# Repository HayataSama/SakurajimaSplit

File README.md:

# SakurajimaSplit

SakurajimaSplit is a 6x3 column stagger split mechanical keyboard. It's inspired by [Corne](https://github.com/foostan/crkbd), [Kyria](https://github.com/splitkb/kyria) and [Elephant42](https://github.com/illness072/elephant42).

> [!NOTE]
> The master branch contains the most recent commits and is not meant for production. Gerbers and production files are available as a github release.
>
> This project was was made in KiCad 9.0 and FreeCAD 1.0. In addition to KiCad's default libraries, I used the [ebastler's marbastlib](https://github.com/ebastler/marbastlib) footprint and symbol library and [zykrah's kicad-kle-placer](https://github.com/zykrah/kicad-kle-placer) plugin. Using other versions may introduce bugs and/or inconsistencies therefore is discouraged.

## Features

- QMK compatible
- Cherry MX switch profile
- 3-Key thumb cluster
- 10-Degree sideways tilt
- SSD1305 OLED display
- W25Q Flash Storage for storing animations
- USB-C connector

## Motivation

I've been interested in mechanical keyboard for a few years now. I got my endgame keyboard (Mode Envoy) a while back and it's been my daily driver since. A while ago I suddenly became interested in split mechanical keyboards. Something about them being tiny and portable, also having this cyberpunky feeling made them appealing to me.

Apparently ortholinear keyboards are also more comfortable to type on. (Not sure how true this is but now that I've built this keyboard and am using it on daily basis, I should say it feels so damn nice to type with!)

I'm also an electrical engineering student and I have some experience designing PCBs. With all these in mind I thought, why not? Why not build a fully custom keyboard, tailored exactly to my needs? A few months later and here we are!

## Why Sakurajima?

Because Mai Sakurajima is the best girl.

## The Journey and Some Notes

This was my first experience designing a keyboard (and a handheld device in general). My approach for designing the layout was to put my fingers on a piece of paper (in the supposedly most comfortable position) and mark under each of my fingertips to find the best position for the home row. Then I measured the distance between keys and rounded them up to the closest standard value. (keyboard "u" units).

For the thumb cluster in addition to the fingertip, I also marked my thumb's joint (MCP joint?) on the paper to find the center of the circle where the thumb keys would be placed. Then I did some basic geometry to find the angle and distance of each key with respect to the center.

I don't know if this is the best approach or even a good approach, but it was fairly easy to do and the end result is great.

Let's talk about electronics. I know I've used a lot a questionable components in this keyboard, one's that are not generally common in keyboards or are not easily found. Believe me, I asked myself this question so many times too! Jokes aside, there were 3 main factors contributing to the component selection. First, this was a one off keyboard that I wanted to make for myself, so price didn't matter. Second, I wanted to try using different parts in my board from what I usually use, to gain more experience about electronics and get a feel for different components. And third (and probably the most important), I live in a heavily sanctioned country, so I don't have easy access to many electronic components because distributors like DigiKey or Mouser don't operate here. I had to work with what was available on the market.

This lead to some weird and frustrating design decisions that I regret.

The first mistake was choosing an SSD1305-based OLED display. I chose this specific display because it's panel was much larger than most common OLED displays on the market and I thought it would look good on the keyboard. The OLED driver is very similar to SSD1306 but is not officially supported by QMK. This is not a big problem by itself as QMK is an open-source firmware and you're free to modify the source code to add support for your display. The main problem is that this OLED module is 128x33 pixels and not 128x32 pixels like most OLED modules are! This creates many memory related issues and incompatibility with QMK which I have yet to solve!

The next not so great decision was choosing a WSON package for hand soldering! The voltage regulator IC is very very tiny and without proper tools like a microscope and a hotplate (which I don't have) is very difficult to hand solder. I don't know what I was thinking when picking parts, but now I've learned (the hard way!) to pay more attention to package sizes.

A big missed opportunity was not making this keyboard wireless. I could probably use an STM32 W-series MCU to make this keyboard Bluetooth-enabled. At the time, I chose to not go this route mainly because I wanted to keep things simple and build something that actually just works. I might create a new revision of this keyboard, fix the stated issues (and some others) and add new features like wireless connectivity in the future.

## Limitations

QMK doesn't currently support W25Q flash storages. I plan on writing a driver for these ICs and add it to QMK in the future, but for now this chip is basically useless.

## Gallery

## Acknowledgements

I have to say a big thank you to [Joe Scotto](https://youtube.com/@joe_scotto) for his YouTube channel which was big source of motivation and guidance in this project and [ebastler](https://github.com/ebastler) for his great KiCad library which made my life a lot easier! Also a big thank you to all the people active in the mechanical keyboard community, open-source contributors and the QMK team!

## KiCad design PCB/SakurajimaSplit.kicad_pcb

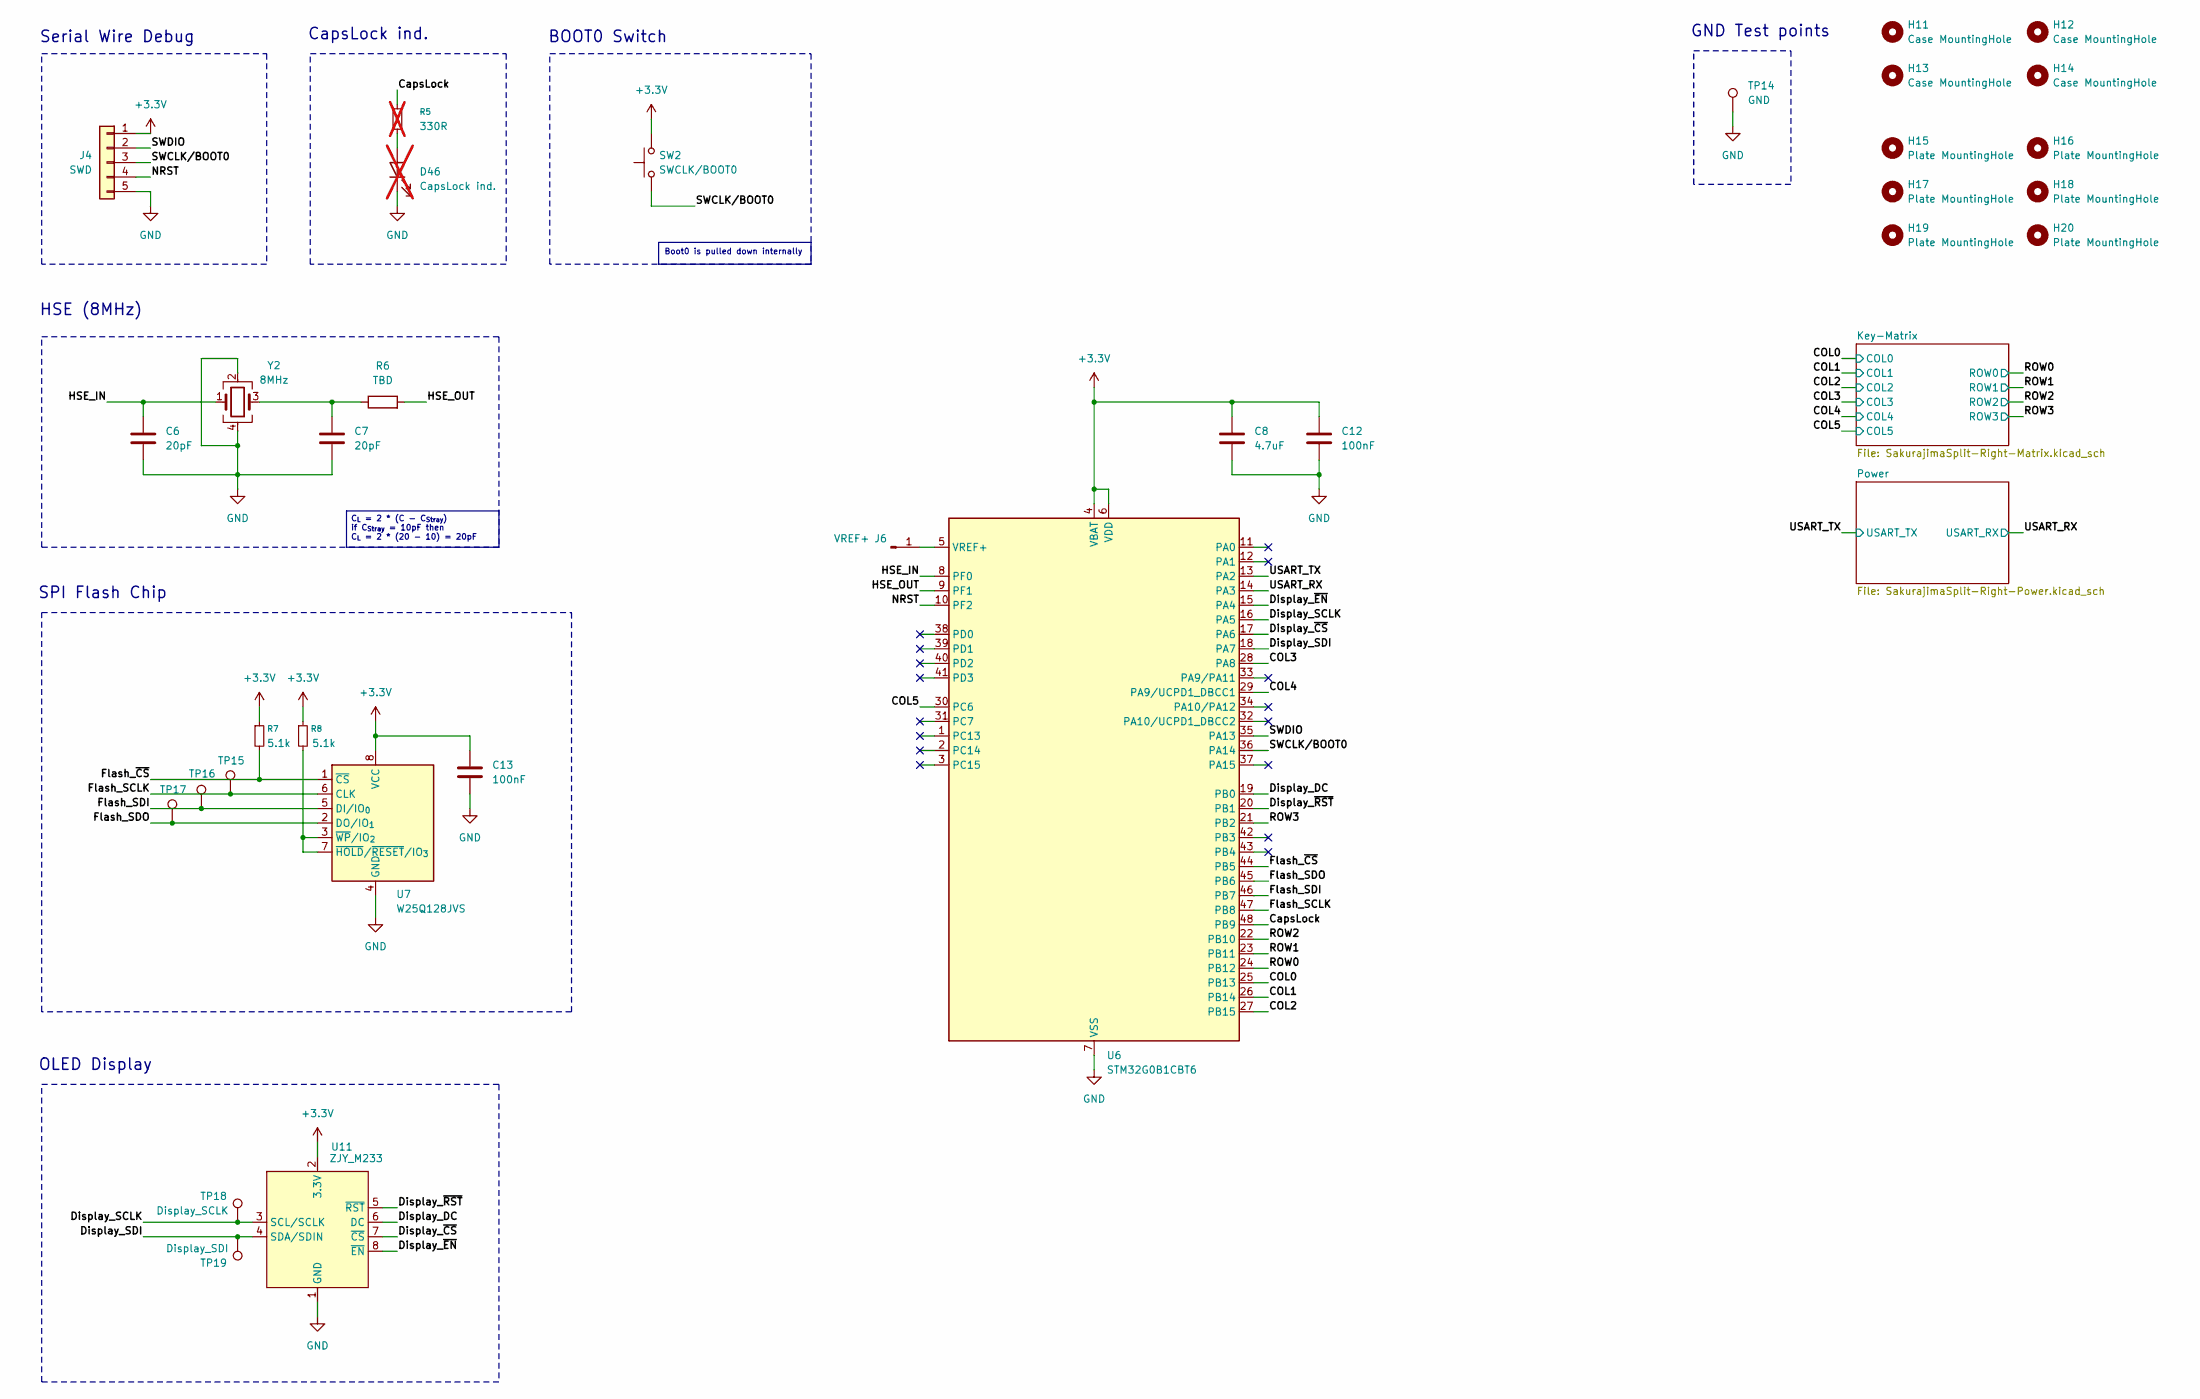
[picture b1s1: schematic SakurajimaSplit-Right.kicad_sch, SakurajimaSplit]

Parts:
C6, C7: 20pF; C_0402_1005Metric_Pad0.74x0.62mm_HandSolder; Manufacturer Part No. GRM1555C1H220JA01D
C8: 4.7uF; C_0805_2012Metric; Manufacturer Part No. GRM21BR61H475KE51L
C12, C13: 100nF; C_0603_1608Metric; Manufacturer Part No. GRM188R72A104KA35D
D46: CapsLock ind.; LED_0603_1608Metric; Manufacturer Part No. XL-1608UWC-04; not fitted
H11, H12, H13, H14: Case MountingHole; MountingHole_3.2mm_M3_Pad_Via
H15, H16, H17, H18, H19, H20: Plate MountingHole; MountingHole_2.2mm_M2_Pad_Via
J4: SWD; PinHeader_1x05_P2.54mm_Horizontal
J6: VREF+; SolderWirePad_1x01_SMD_1x2mm
R5: 330R; R_0603_1608Metric; Manufacturer Part No. SER0603F330R; not fitted
R6: TBD; R_0603_1608Metric
R7, R8: 5.1k; R_0603_1608Metric; Manufacturer Part No. 0603WAF5101T5E
SW2: SWCLK/BOOT0; SW_Push_TS-1010B; Manufacturer Part No. TS-1010B-B-A
TP14: GND; TestPoint_Pad_Circular_1.3mm
TP15: Flash_SCLK; TestPoint_Pad_Circular_1.3mm
TP16: Flash_SDI; TestPoint_Pad_Circular_1.3mm
TP17: Flash_SDO; TestPoint_Pad_Circular_1.3mm
TP18: Display_SCLK; TestPoint_Pad_Circular_1.3mm
TP19: Display_SDI; TestPoint_Pad_Circular_1.3mm
U6: STM32G0B1CBT6; LQFP-48_7x7mm_P0.5mm; Manufacturer Part No. STM32G0B1CBT6
U7: W25Q128JVS; SOIC-8_5.3x5.3mm_P1.27mm; Manufacturer Part No. W25Q128JVSIQ
U11: ZJY_M233; OLED_SSD1305
Y2: 8MHz; Crystal_SMD_3225-4Pin_3.2x2.5mm; Manufacturer Part No. X32258MSB4SI

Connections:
+3.3V: C8.1, C12.1, C13.1, J4.1, R7.1, R8.1, SW2.2, U6.4 (VBAT), U6.6 (VDD), U7.8 (VCC), U11.2 (3.3V); also elsewhere on the board
/Right-Half/COL0: U6.25 (PB13); also elsewhere on the board
/Right-Half/COL1: U6.26 (PB14); also elsewhere on the board
/Right-Half/COL2: U6.27 (PB15); also elsewhere on the board
/Right-Half/COL3: U6.28 (PA8); also elsewhere on the board
/Right-Half/COL4: U6.29 (PA9/UCPD1_DBCC1); also elsewhere on the board
/Right-Half/COL5: U6.30 (PC6); also elsewhere on the board
/Right-Half/CapsLock: R5.1, U6.48 (PB9)
/Right-Half/Display_DC: U6.19 (PB0), U11.6 (DC)
/Right-Half/Display_SCLK: TP18.1, U6.16 (PA5), U11.3 (SCL/SCLK)
/Right-Half/Display_SDI: TP19.1, U6.18 (PA7), U11.4 (SDA/SDIN)
/Right-Half/Display_~CS: U6.17 (PA6), U11.7 (~CS)
/Right-Half/Display_~EN: U6.15 (PA4), U11.8 (~EN)
/Right-Half/Display_~RST: U6.20 (PB1), U11.5 (~RST)
/Right-Half/Flash_SCLK: TP15.1, U6.47 (PB8), U7.6 (CLK)
/Right-Half/Flash_SDI: TP16.1, U6.46 (PB7), U7.5 (DI/IO_{0})
/Right-Half/Flash_SDO: TP17.1, U6.45 (PB6), U7.2 (DO/IO_{1})
/Right-Half/Flash_~CS: R7.2, U6.44 (PB5), U7.1 (~CS)
/Right-Half/HSE_IN: C6.1, U6.8 (PF0), Y2.1
/Right-Half/HSE_OUT: R6.2, U6.9 (PF1)
/Right-Half/NRST: J4.4, U6.10 (PF2)
/Right-Half/ROW0: U6.24 (PB12); also elsewhere on the board
/Right-Half/ROW1: U6.23 (PB11); also elsewhere on the board
/Right-Half/ROW2: U6.22 (PB10); also elsewhere on the board
/Right-Half/ROW3: U6.21 (PB2); also elsewhere on the board
/Right-Half/SWCLK/BOOT0: J4.3, SW2.1, U6.36 (PA14)
/Right-Half/SWDIO: J4.2, U6.35 (PA13)
/Right-Half/USART_RX: U6.14 (PA3); also elsewhere on the board
/Right-Half/USART_TX: U6.13 (PA2); also elsewhere on the board
GND: C6.2, C7.2, C8.2, C12.2, C13.2, D46.1 (K), J4.5, TP14.1, U6.7 (VSS), U7.4 (GND), U11.1 (GND), Y2.2, Y2.4; also elsewhere on the board
unnamed: C7.1, R6.1, Y2.3
unnamed: D46.2 (A), R5.2
unnamed: J6.1, U6.5 (VREF+)
unnamed: R8.2, U7.3 (~WP/IO_{2}), U7.7 (~HOLD/~RESET/IO_{3})

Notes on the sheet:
HSE (8MHz)
SPI Flash Chip
Serial Wire Debug
BOOT0 Switch
OLED Display
GND Test points
CapsLock ind.
Boot0 is pulled down internally
C_{L} = 2 * (C - C_{Stray}) if C_{Stray} = 10pF then C_{L} = 2 * (20 - 10) = 20pF

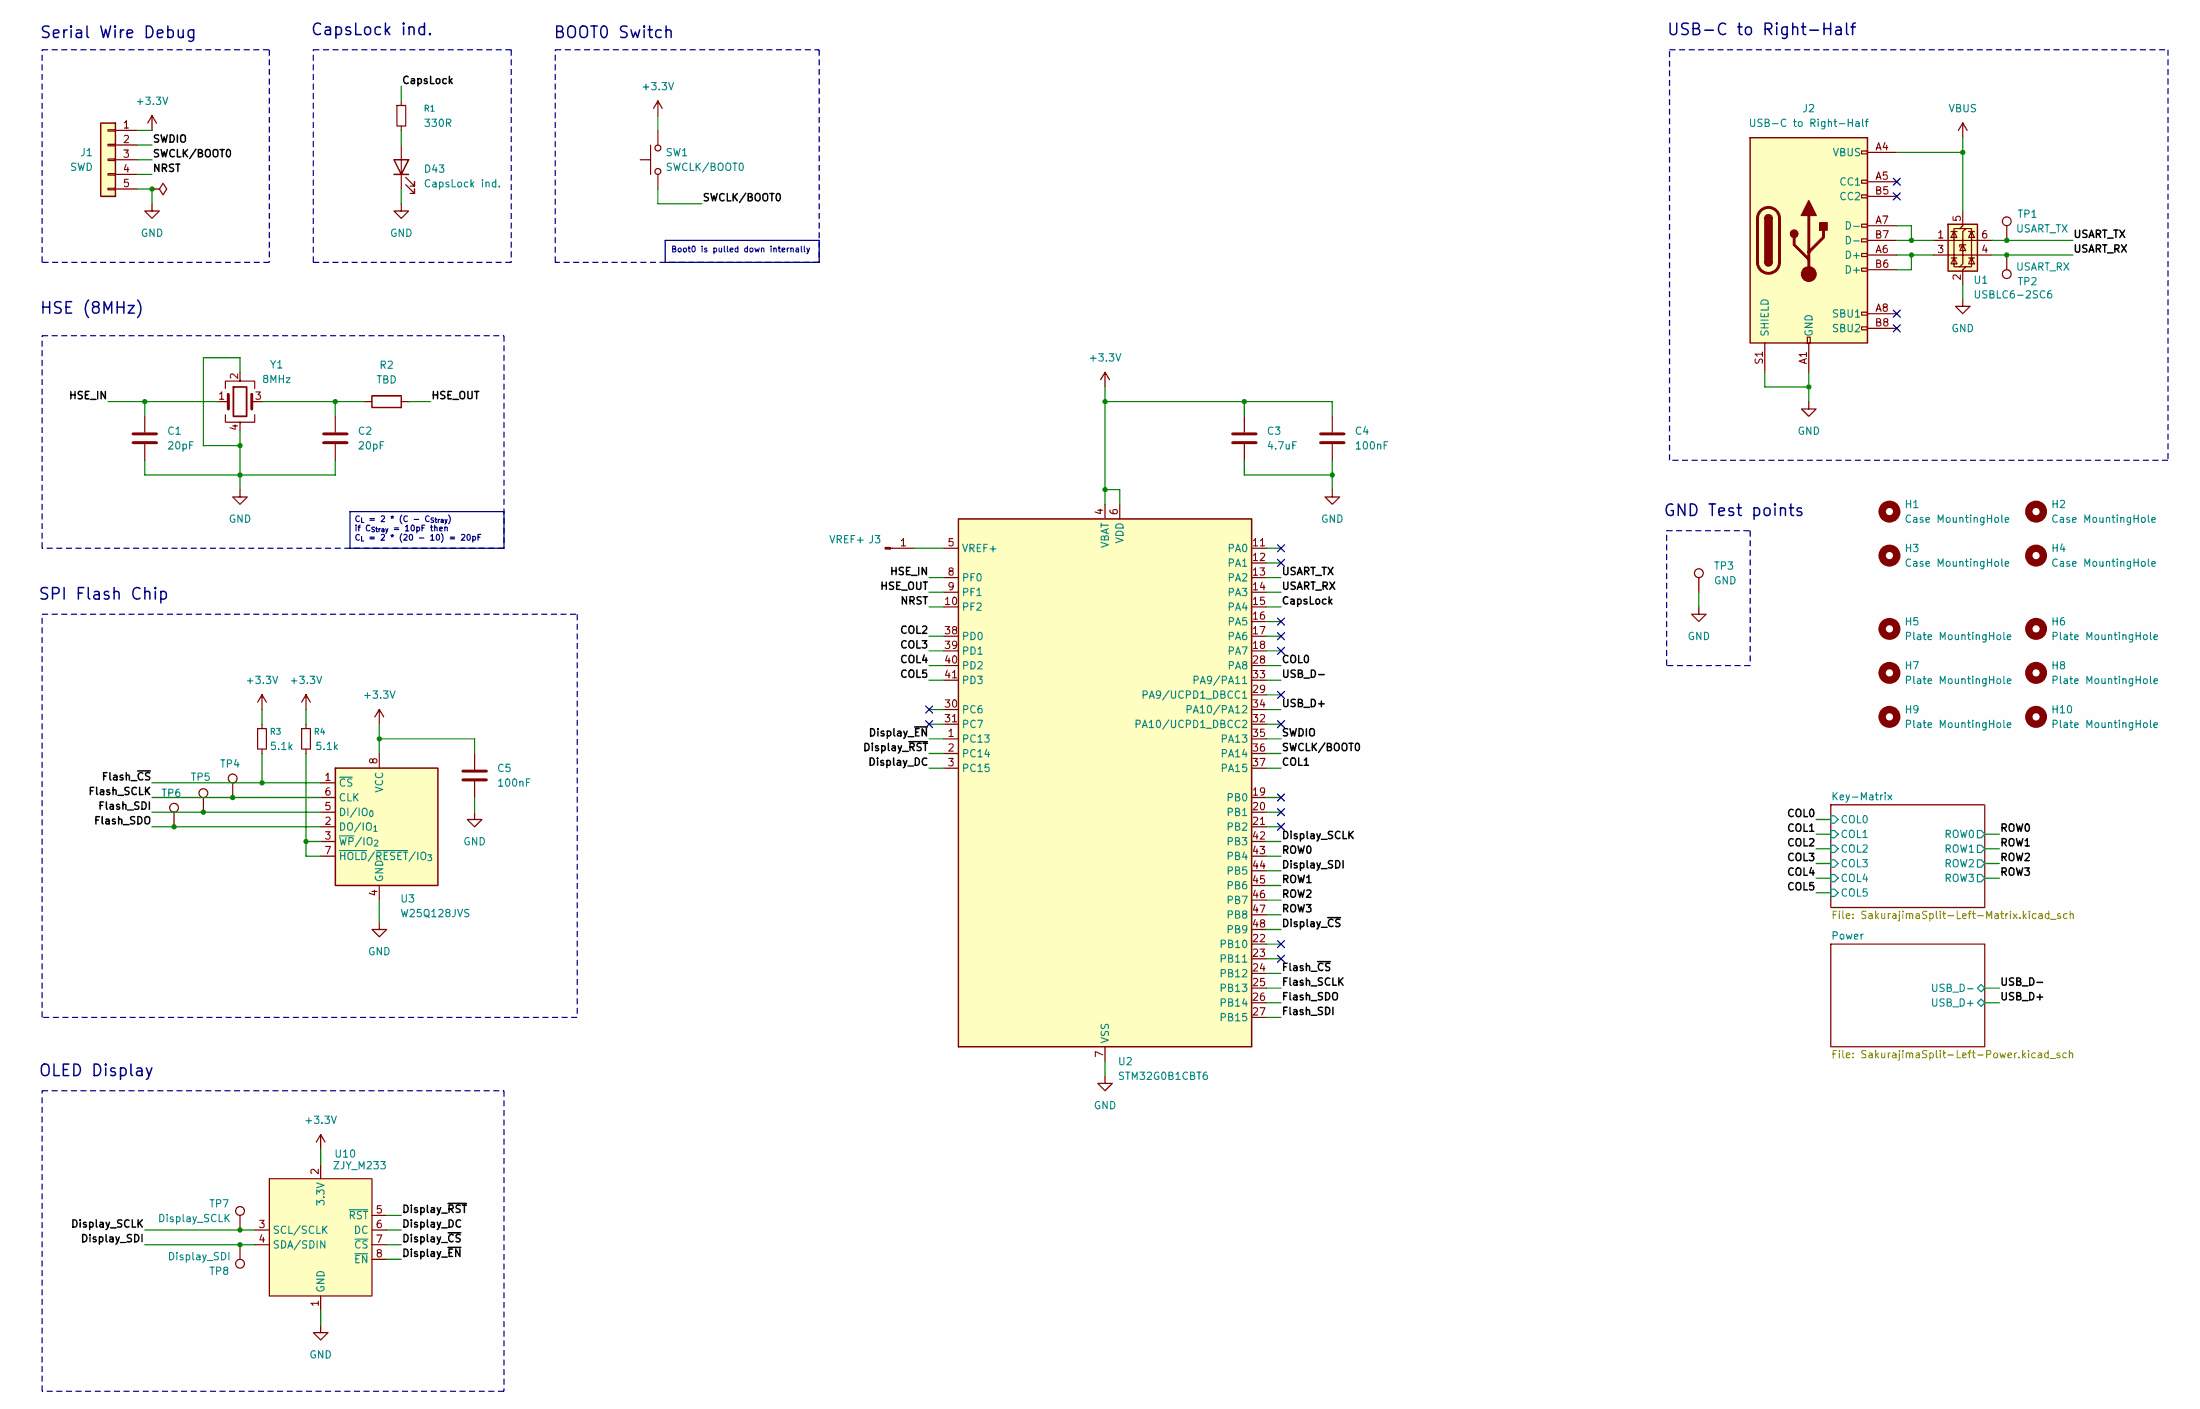
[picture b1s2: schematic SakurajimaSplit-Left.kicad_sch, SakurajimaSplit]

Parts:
C1, C2: 20pF; C_0402_1005Metric_Pad0.74x0.62mm_HandSolder; Manufacturer Part No. GRM1555C1H220JA01D
C3: 4.7uF; C_0805_2012Metric; Manufacturer Part No. GRM21BR61H475KE51L
C4, C5: 100nF; C_0603_1608Metric; Manufacturer Part No. GRM188R72A104KA35D
D43: CapsLock ind.; LED_0603_1608Metric; Manufacturer Part No. XL-1608UWC-04
H1, H2, H3, H4: Case MountingHole; MountingHole_3.2mm_M3_Pad_Via
H5, H6, H7, H8, H9, H10: Plate MountingHole; MountingHole_2.2mm_M2_Pad_Via
J1: SWD; PinHeader_1x05_P2.54mm_Horizontal
J2: USB-C to Right-Half; USB_C_Receptacle_G-Switch_GT-USB-7010ASV; Manufacturer Part No. GT-USB-7010ASV
J3: VREF+; SolderWirePad_1x01_SMD_1x2mm
R1: 330R; R_0603_1608Metric; Manufacturer Part No. SER0603F330R
R2: TBD; R_0603_1608Metric
R3, R4: 5.1k; R_0603_1608Metric; Manufacturer Part No. 0603WAF5101T5E
SW1: SWCLK/BOOT0; SW_Push_TS-1010B; Manufacturer Part No. TS-1010B-B-A
TP1: USART_TX; TestPoint_Pad_Circular_1.3mm
TP2: USART_RX; TestPoint_Pad_Circular_1.3mm
TP3: GND; TestPoint_Pad_Circular_1.3mm
TP4: Flash_SCLK; TestPoint_Pad_Circular_1.3mm
TP5: Flash_SDI; TestPoint_Pad_Circular_1.3mm
TP6: Flash_SDO; TestPoint_Pad_Circular_1.3mm
TP7: Display_SCLK; TestPoint_Pad_Circular_1.3mm
TP8: Display_SDI; TestPoint_Pad_Circular_1.3mm
U1: USBLC6-2SC6; SOT-23-6; Manufacturer Part No. USBLC6-4SC6
U2: STM32G0B1CBT6; LQFP-48_7x7mm_P0.5mm; Manufacturer Part No. STM32G0B1CBT6
U3: W25Q128JVS; SOIC-8_5.3x5.3mm_P1.27mm; Manufacturer Part No. W25Q128JVSIQ
U10: ZJY_M233; OLED_SSD1305
Y1: 8MHz; Crystal_SMD_3225-4Pin_3.2x2.5mm; Manufacturer Part No. X32258MSB4SI

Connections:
+3.3V: C3.1, C4.1, C5.1, J1.1, R3.1, R4.1, SW1.2, U2.4 (VBAT), U2.6 (VDD), U3.8 (VCC), U10.2 (3.3V); also elsewhere on the board
/Left-Half/COL0: U2.28 (PA8); also elsewhere on the board
/Left-Half/COL1: U2.37 (PA15); also elsewhere on the board
/Left-Half/COL2: U2.38 (PD0); also elsewhere on the board
/Left-Half/COL3: U2.39 (PD1); also elsewhere on the board
/Left-Half/COL4: U2.40 (PD2); also elsewhere on the board
/Left-Half/COL5: U2.41 (PD3); also elsewhere on the board
/Left-Half/CapsLock: R1.1, U2.15 (PA4)
/Left-Half/Display_DC: U2.3 (PC15), U10.6 (DC)
/Left-Half/Display_SCLK: TP7.1, U2.42 (PB3), U10.3 (SCL/SCLK)
/Left-Half/Display_SDI: TP8.1, U2.44 (PB5), U10.4 (SDA/SDIN)
/Left-Half/Display_~CS: U2.48 (PB9), U10.7 (~CS)
/Left-Half/Display_~EN: U2.1 (PC13), U10.8 (~EN)
/Left-Half/Display_~RST: U2.2 (PC14), U10.5 (~RST)
/Left-Half/Flash_SCLK: TP4.1, U2.25 (PB13), U3.6 (CLK)
/Left-Half/Flash_SDI: TP5.1, U2.27 (PB15), U3.5 (DI/IO_{0})
/Left-Half/Flash_SDO: TP6.1, U2.26 (PB14), U3.2 (DO/IO_{1})
/Left-Half/Flash_~CS: R3.2, U2.24 (PB12), U3.1 (~CS)
/Left-Half/HSE_IN: C1.1, U2.8 (PF0), Y1.1
/Left-Half/HSE_OUT: R2.2, U2.9 (PF1)
/Left-Half/NRST: J1.4, U2.10 (PF2)
/Left-Half/ROW0: U2.43 (PB4); also elsewhere on the board
/Left-Half/ROW1: U2.45 (PB6); also elsewhere on the board
/Left-Half/ROW2: U2.46 (PB7); also elsewhere on the board
/Left-Half/ROW3: U2.47 (PB8); also elsewhere on the board
/Left-Half/SWCLK/BOOT0: J1.3, SW1.1, U2.36 (PA14)
/Left-Half/SWDIO: J1.2, U2.35 (PA13)
/Left-Half/USART_RX: TP2.1, U1.4 (I/O2), U2.14 (PA3)
/Left-Half/USART_TX: TP1.1, U1.6 (I/O1), U2.13 (PA2)
/Left-Half/USB_D+: U2.34 (PA10/PA12); also elsewhere on the board
/Left-Half/USB_D-: U2.33 (PA9/PA11); also elsewhere on the board
GND: C1.2, C2.2, C3.2, C4.2, C5.2, D43.1 (K), J1.5, J2.A1 (GND), J2.A12 (GND), J2.B1 (GND), J2.B12 (GND), J2.S1 (SHIELD), TP3.1, U1.2 (GND), U2.7 (VSS), U3.4 (GND), U10.1 (GND), Y1.2, Y1.4; also elsewhere on the board
unnamed: C2.1, R2.1, Y1.3
unnamed: D43.2 (A), R1.2
unnamed: J2.A6 (D+), J2.B6 (D+), U1.3 (I/O2)
unnamed: J2.A7 (D-), J2.B7 (D-), U1.1 (I/O1)
unnamed: J3.1, U2.5 (VREF+)
unnamed: R4.2, U3.3 (~WP/IO_{2}), U3.7 (~HOLD/~RESET/IO_{3})
VBUS: J2.A4 (VBUS), J2.A9 (VBUS), J2.B4 (VBUS), J2.B9 (VBUS), U1.5 (VBUS); also elsewhere on the board

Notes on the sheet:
HSE (8MHz)
USB-C to Right-Half
SPI Flash Chip
GND Test points
Serial Wire Debug
CapsLock ind.
BOOT0 Switch
OLED Display
C_{L} = 2 * (C - C_{Stray}) if C_{Stray} = 10pF then C_{L} = 2 * (20 - 10) = 20pF
Boot0 is pulled down internally

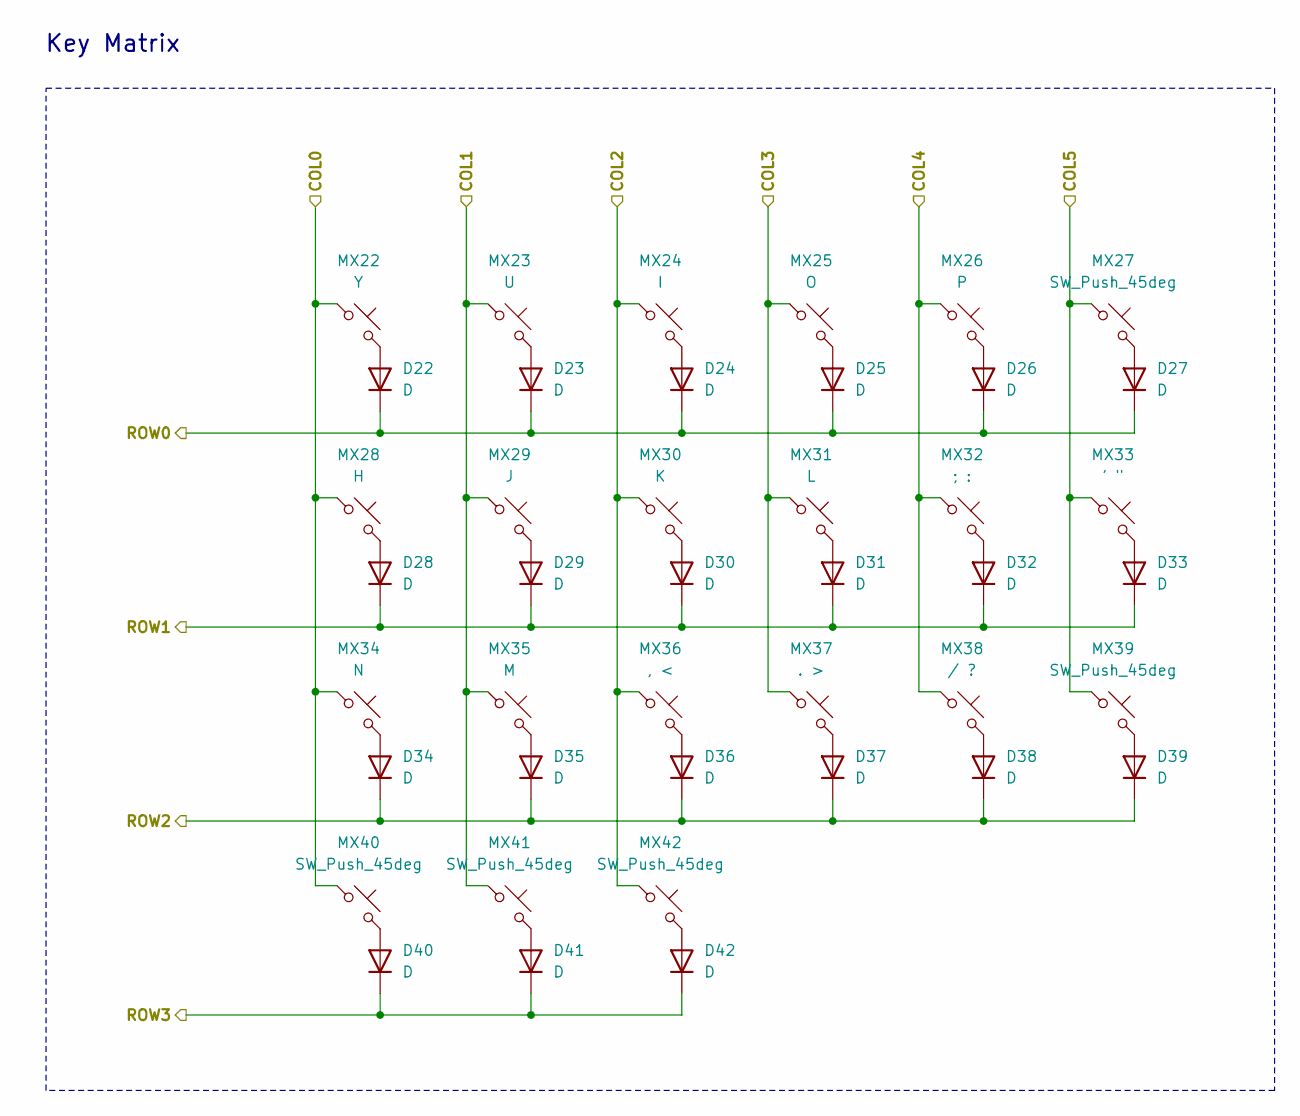
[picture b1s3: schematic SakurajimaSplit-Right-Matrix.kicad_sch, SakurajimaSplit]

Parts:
D22, D23, D24, D25, D26, D27, D28, D29, D30, D31, D32, D33, D34, D35, D36, D37, D38, D39, D40, D41, D42: D; D_SOD-123; Manufacturer Part No. 1N4148W
MX22: Y; SW_MX_1u
MX23: U; SW_MX_1u
MX24: I; SW_MX_1u
MX25: O; SW_MX_1u
MX26: P; SW_MX_1u
MX27, MX39, MX41, MX42: SW_Push_45deg; SW_MX_1u
MX28: H; SW_MX_1u
MX29: J; SW_MX_1u
MX30: K; SW_MX_1u
MX31: L; SW_MX_1u
MX32: ; :; SW_MX_1u
MX33: ' "; SW_MX_1u
MX34: N; SW_MX_1u
MX35: M; SW_MX_1u
MX36: , <; SW_MX_1u
MX37: . >; SW_MX_1u
MX38: / ?; SW_MX_1u
MX40: SW_Push_45deg; SW_MX_1.5u

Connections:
/Right-Half/COL0: MX22.1, MX28.1, MX34.1, MX40.1; also elsewhere on the board
/Right-Half/COL1: MX23.1, MX29.1, MX35.1, MX41.1; also elsewhere on the board
/Right-Half/COL2: MX24.1, MX30.1, MX36.1, MX42.1; also elsewhere on the board
/Right-Half/COL3: MX25.1, MX31.1, MX37.1; also elsewhere on the board
/Right-Half/COL4: MX26.1, MX32.1, MX38.1; also elsewhere on the board
/Right-Half/COL5: MX27.1, MX33.1, MX39.1; also elsewhere on the board
/Right-Half/ROW0: D22.1 (K), D23.1 (K), D24.1 (K), D25.1 (K), D26.1 (K), D27.1 (K); also elsewhere on the board
/Right-Half/ROW1: D28.1 (K), D29.1 (K), D30.1 (K), D31.1 (K), D32.1 (K), D33.1 (K); also elsewhere on the board
/Right-Half/ROW2: D34.1 (K), D35.1 (K), D36.1 (K), D37.1 (K), D38.1 (K), D39.1 (K); also elsewhere on the board
/Right-Half/ROW3: D40.1 (K), D41.1 (K), D42.1 (K); also elsewhere on the board
unnamed: D22.2 (A), MX22.2
unnamed: D23.2 (A), MX23.2
unnamed: D24.2 (A), MX24.2
unnamed: D25.2 (A), MX25.2
unnamed: D26.2 (A), MX26.2
unnamed: D27.2 (A), MX27.2
unnamed: D28.2 (A), MX28.2
unnamed: D29.2 (A), MX29.2
unnamed: D30.2 (A), MX30.2
unnamed: D31.2 (A), MX31.2
unnamed: D32.2 (A), MX32.2
unnamed: D33.2 (A), MX33.2
unnamed: D34.2 (A), MX34.2
unnamed: D35.2 (A), MX35.2
unnamed: D36.2 (A), MX36.2
unnamed: D37.2 (A), MX37.2
unnamed: D38.2 (A), MX38.2
unnamed: D39.2 (A), MX39.2
unnamed: D40.2 (A), MX40.2
unnamed: D41.2 (A), MX41.2
unnamed: D42.2 (A), MX42.2

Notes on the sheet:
Key Matrix

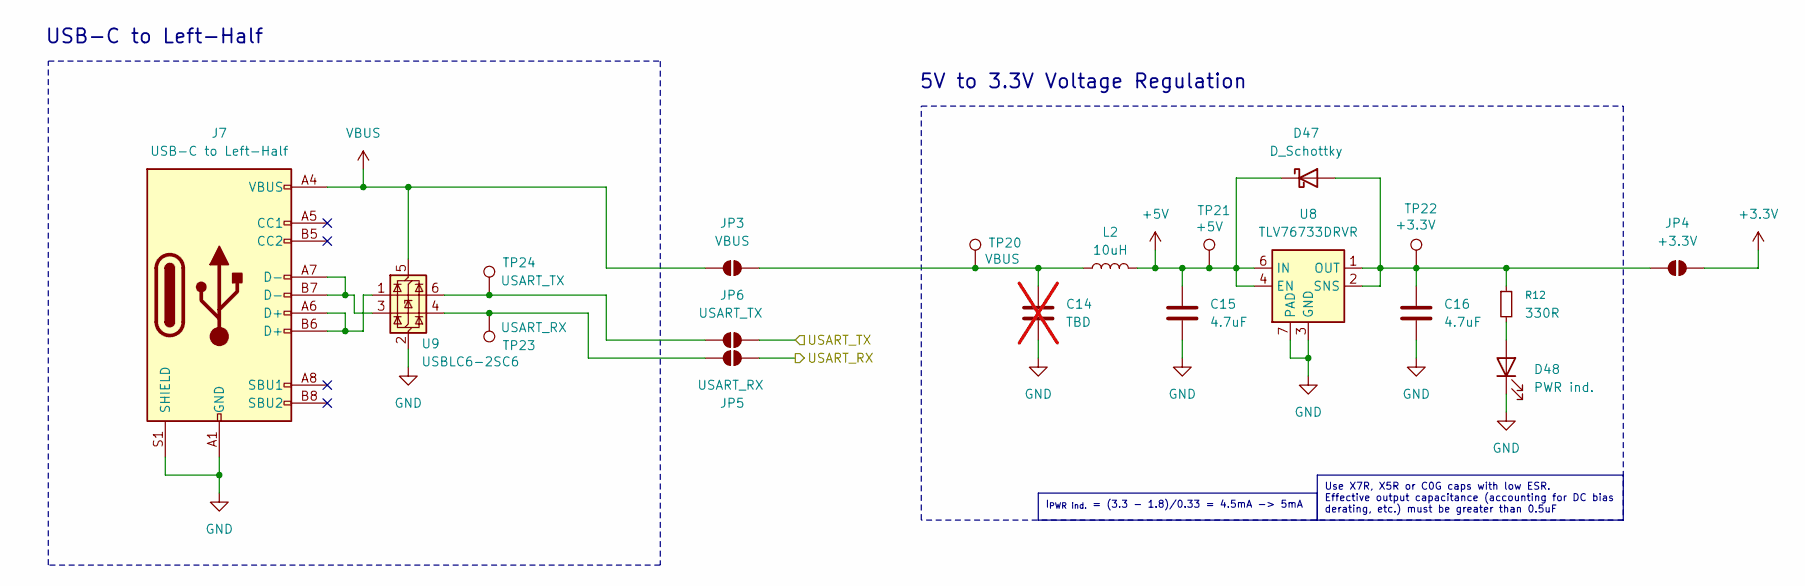
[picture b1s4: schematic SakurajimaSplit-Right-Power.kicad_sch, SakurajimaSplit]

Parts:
C14: TBD; C_0805_2012Metric; Manufacturer Part No. GRM21BR61H475KE51L; not fitted
C15, C16: 4.7uF; C_0805_2012Metric; Manufacturer Part No. GRM21BR61H475KE51L
D47: D_Schottky; D_SOD-123; Manufacturer Part No. B0530W-7-F
D48: PWR ind.; LED_0603_1608Metric; Manufacturer Part No. XL-1608UGC-04
J7: USB-C to Left-Half; USB_C_Receptacle_G-Switch_GT-USB-7010ASV; Manufacturer Part No. GT-USB-7010ASV
JP3: VBUS; SolderJumper-2_P1.3mm_Open_TrianglePad1.0x1.5mm
JP4: +3.3V; SolderJumper-2_P1.3mm_Open_TrianglePad1.0x1.5mm
JP5: USART_RX; SolderJumper-2_P1.3mm_Open_TrianglePad1.0x1.5mm
JP6: USART_TX; SolderJumper-2_P1.3mm_Open_TrianglePad1.0x1.5mm
L2: 10uH; L_1210_3225Metric; Manufacturer Part No. DFE322512F-100M
R12: 330R; R_0603_1608Metric; Manufacturer Part No. SER0603F330R
TP20: VBUS; TestPoint_Pad_Circular_1.3mm
TP21: +5V; TestPoint_Pad_Circular_1.3mm
TP22: +3.3V; TestPoint_Pad_Circular_1.3mm
TP23: USART_RX; TestPoint_Pad_Circular_1.3mm
TP24: USART_TX; TestPoint_Pad_Circular_1.3mm
U8: TLV76733DRVR; WSON-6-1EP_2x2mm_P0.65mm_EP1x1.6mm_ThermalVias; Manufacturer Part No. TLV76733DRVR
U9: USBLC6-2SC6; SOT-23-6; Manufacturer Part No. USBLC6-4SC6

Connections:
+3.3V: JP4.2 (B); also elsewhere on the board
+5V: C15.1, D47.1 (K), L2.2, TP21.1, U8.4 (EN), U8.6 (IN); also elsewhere on the board
/Right-Half/USART_RX: JP5.2 (B); also elsewhere on the board
/Right-Half/USART_TX: JP6.2 (B); also elsewhere on the board
GND: C14.2, C15.2, C16.2, D48.1 (K), J7.A1 (GND), J7.A12 (GND), J7.B1 (GND), J7.B12 (GND), J7.S1 (SHIELD), U8.3 (GND), U8.5 (GND), U8.7 (PAD), U9.2 (GND); also elsewhere on the board
unnamed: C16.1, D47.2 (A), JP4.1 (A), R12.1, TP22.1, U8.1 (OUT), U8.2 (SNS)
unnamed: D48.2 (A), R12.2
unnamed: J7.A6 (D+), J7.B6 (D+), U9.1 (I/O1)
unnamed: J7.A7 (D-), J7.B7 (D-), U9.3 (I/O2)
unnamed: C14.1, JP3.2 (B), L2.1, TP20.1
unnamed: JP5.1 (A), TP23.1, U9.4 (I/O2)
unnamed: JP6.1 (A), TP24.1, U9.6 (I/O1)
VBUS: J7.A4 (VBUS), J7.A9 (VBUS), J7.B4 (VBUS), J7.B9 (VBUS), JP3.1 (A), U9.5 (VBUS); also elsewhere on the board

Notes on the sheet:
USB-C to Left-Half
5V to 3.3V Voltage Regulation
Use X7R, X5R or C0G caps with low ESR. Effective output capacitance (accounting for DC bias derating, etc.) must be greater than 0.5uF
I_{PWR ind.} = (3.3 - 1.8)/0.33 = 4.5mA -> 5mA

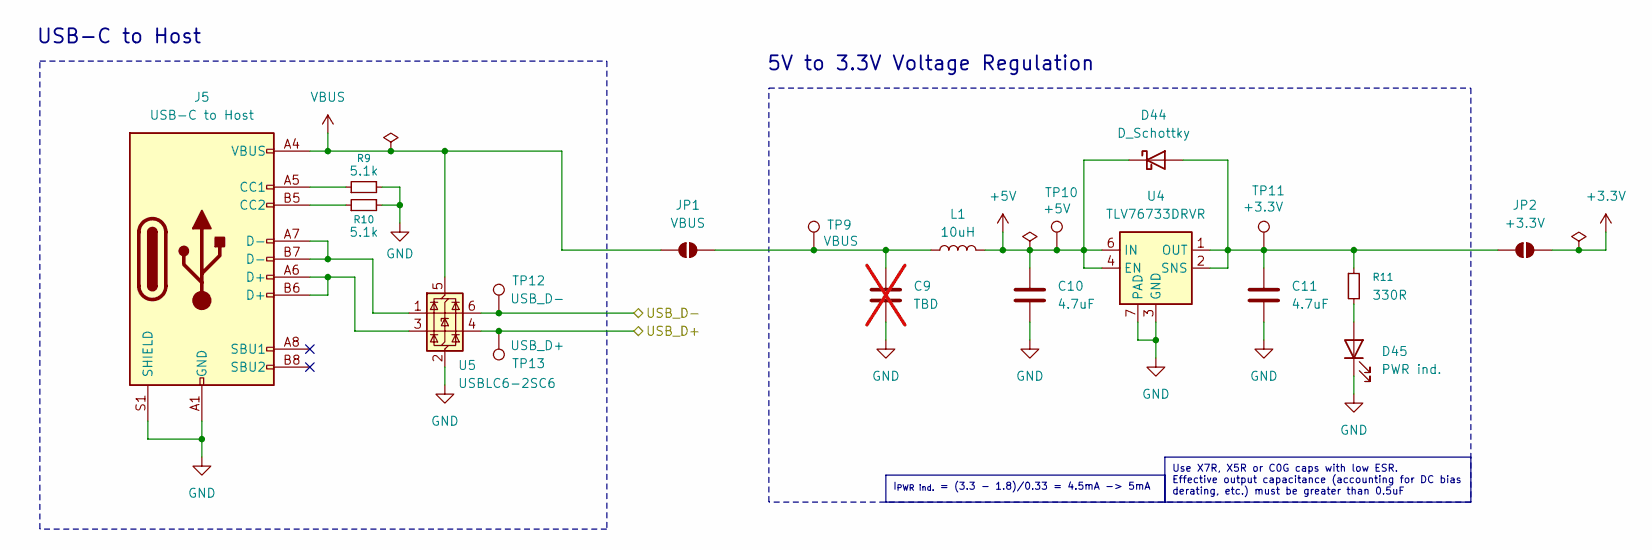
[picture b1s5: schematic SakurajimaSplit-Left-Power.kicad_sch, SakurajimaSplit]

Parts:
C9: TBD; C_0805_2012Metric; Manufacturer Part No. GRM21BR61H475KE51L; not fitted
C10, C11: 4.7uF; C_0805_2012Metric; Manufacturer Part No. GRM21BR61H475KE51L
D44: D_Schottky; D_SOD-123; Manufacturer Part No. B0530W-7-F
D45: PWR ind.; LED_0603_1608Metric; Manufacturer Part No. XL-1608UGC-04
J5: USB-C to Host; USB_C_Receptacle_G-Switch_GT-USB-7010ASV; Manufacturer Part No. GT-USB-7010ASV
JP1: VBUS; SolderJumper-2_P1.3mm_Open_TrianglePad1.0x1.5mm
JP2: +3.3V; SolderJumper-2_P1.3mm_Open_TrianglePad1.0x1.5mm
L1: 10uH; L_1210_3225Metric; Manufacturer Part No. DFE322512F-100M
R9, R10: 5.1k; R_0603_1608Metric; Manufacturer Part No. 0603WAF5101T5E
R11: 330R; R_0603_1608Metric; Manufacturer Part No. SER0603F330R
TP9: VBUS; TestPoint_Pad_Circular_1.3mm
TP10: +5V; TestPoint_Pad_Circular_1.3mm
TP11: +3.3V; TestPoint_Pad_Circular_1.3mm
TP12: USB_D-; TestPoint_Pad_Circular_1.3mm
TP13: USB_D+; TestPoint_Pad_Circular_1.3mm
U4: TLV76733DRVR; WSON-6-1EP_2x2mm_P0.65mm_EP1x1.6mm_ThermalVias; Manufacturer Part No. TLV76733DRVR
U5: USBLC6-2SC6; SOT-23-6; Manufacturer Part No. USBLC6-4SC6

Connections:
+3.3V: JP2.2 (B); also elsewhere on the board
+5V: C10.1, D44.1 (K), L1.2, TP10.1, U4.4 (EN), U4.6 (IN); also elsewhere on the board
/Left-Half/USB_D+: TP13.1, U5.4 (I/O2); also elsewhere on the board
/Left-Half/USB_D-: TP12.1, U5.6 (I/O1); also elsewhere on the board
GND: C9.2, C10.2, C11.2, D45.1 (K), J5.A1 (GND), J5.A12 (GND), J5.B1 (GND), J5.B12 (GND), J5.S1 (SHIELD), R9.2, R10.2, U4.3 (GND), U4.5 (GND), U4.7 (PAD), U5.2 (GND); also elsewhere on the board
unnamed: C11.1, D44.2 (A), JP2.1 (A), R11.1, TP11.1, U4.1 (OUT), U4.2 (SNS)
unnamed: D45.2 (A), R11.2
unnamed: J5.A5 (CC1), R9.1
unnamed: J5.B5 (CC2), R10.1
unnamed: J5.A6 (D+), J5.B6 (D+), U5.3 (I/O2)
unnamed: J5.A7 (D-), J5.B7 (D-), U5.1 (I/O1)
unnamed: C9.1, JP1.2 (B), L1.1, TP9.1
VBUS: J5.A4 (VBUS), J5.A9 (VBUS), J5.B4 (VBUS), J5.B9 (VBUS), JP1.1 (A), U5.5 (VBUS); also elsewhere on the board

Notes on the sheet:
5V to 3.3V Voltage Regulation
USB-C to Host
I_{PWR ind.} = (3.3 - 1.8)/0.33 = 4.5mA -> 5mA
Use X7R, X5R or C0G caps with low ESR. Effective output capacitance (accounting for DC bias derating, etc.) must be greater than 0.5uF

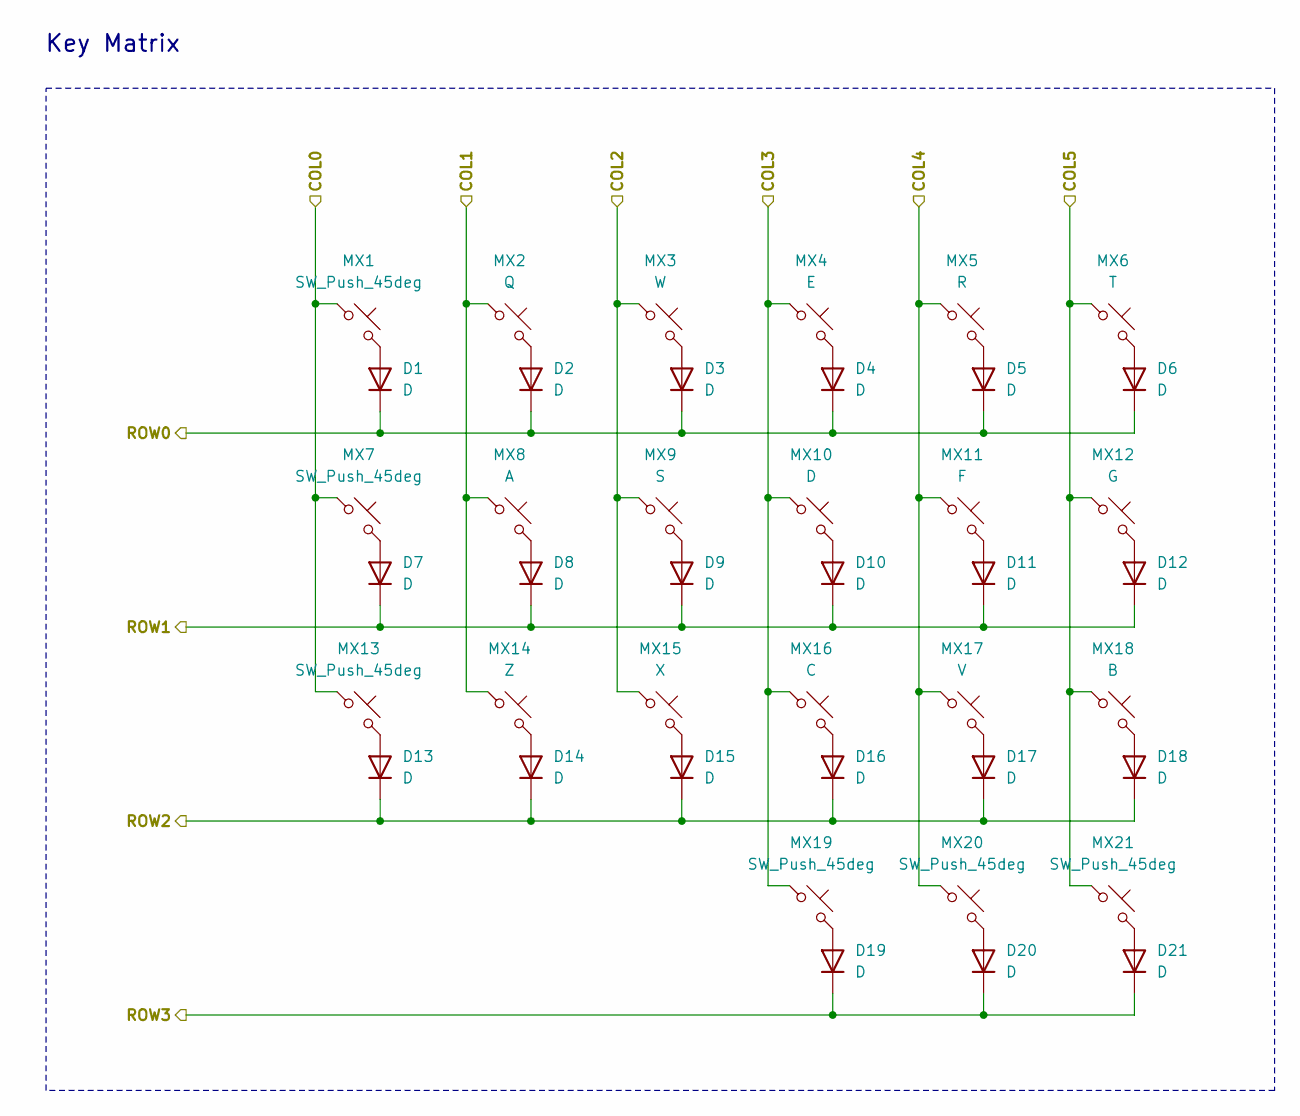
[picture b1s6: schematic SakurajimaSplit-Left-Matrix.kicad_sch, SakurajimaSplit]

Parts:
D1, D2, D3, D4, D5, D6, D7, D8, D9, D10, D11, D12, D13, D14, D15, D16, D17, D18, D19, D20, D21: D; D_SOD-123; Manufacturer Part No. 1N4148W
MX1, MX7, MX13, MX19, MX20: SW_Push_45deg; SW_MX_1u
MX2: Q; SW_MX_1u
MX3: W; SW_MX_1u
MX4: E; SW_MX_1u
MX5: R; SW_MX_1u
MX6: T; SW_MX_1u
MX8: A; SW_MX_1u
MX9: S; SW_MX_1u
MX10: D; SW_MX_1u
MX11: F; SW_MX_1u
MX12: G; SW_MX_1u
MX14: Z; SW_MX_1u
MX15: X; SW_MX_1u
MX16: C; SW_MX_1u
MX17: V; SW_MX_1u
MX18: B; SW_MX_1u
MX21: SW_Push_45deg; SW_MX_1.5u

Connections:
/Left-Half/COL0: MX1.1, MX7.1, MX13.1; also elsewhere on the board
/Left-Half/COL1: MX2.1, MX8.1, MX14.1; also elsewhere on the board
/Left-Half/COL2: MX3.1, MX9.1, MX15.1; also elsewhere on the board
/Left-Half/COL3: MX4.1, MX10.1, MX16.1, MX19.1; also elsewhere on the board
/Left-Half/COL4: MX5.1, MX11.1, MX17.1, MX20.1; also elsewhere on the board
/Left-Half/COL5: MX6.1, MX12.1, MX18.1, MX21.1; also elsewhere on the board
/Left-Half/ROW0: D1.1 (K), D2.1 (K), D3.1 (K), D4.1 (K), D5.1 (K), D6.1 (K); also elsewhere on the board
/Left-Half/ROW1: D7.1 (K), D8.1 (K), D9.1 (K), D10.1 (K), D11.1 (K), D12.1 (K); also elsewhere on the board
/Left-Half/ROW2: D13.1 (K), D14.1 (K), D15.1 (K), D16.1 (K), D17.1 (K), D18.1 (K); also elsewhere on the board
/Left-Half/ROW3: D19.1 (K), D20.1 (K), D21.1 (K); also elsewhere on the board
unnamed: D1.2 (A), MX1.2
unnamed: D2.2 (A), MX2.2
unnamed: D3.2 (A), MX3.2
unnamed: D4.2 (A), MX4.2
unnamed: D5.2 (A), MX5.2
unnamed: D6.2 (A), MX6.2
unnamed: D7.2 (A), MX7.2
unnamed: D8.2 (A), MX8.2
unnamed: D9.2 (A), MX9.2
unnamed: D10.2 (A), MX10.2
unnamed: D11.2 (A), MX11.2
unnamed: D12.2 (A), MX12.2
unnamed: D13.2 (A), MX13.2
unnamed: D14.2 (A), MX14.2
unnamed: D15.2 (A), MX15.2
unnamed: D16.2 (A), MX16.2
unnamed: D17.2 (A), MX17.2
unnamed: D18.2 (A), MX18.2
unnamed: D19.2 (A), MX19.2
unnamed: D20.2 (A), MX20.2
unnamed: D21.2 (A), MX21.2

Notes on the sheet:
Key Matrix
